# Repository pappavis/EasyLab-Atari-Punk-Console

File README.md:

Een poging om retro 'n 6581-SID chip na te bou met 555-timers ICs.<br/>
== Atari Punk Console
Ontwerp: Michiel Erasmus

<br/>
<br/>

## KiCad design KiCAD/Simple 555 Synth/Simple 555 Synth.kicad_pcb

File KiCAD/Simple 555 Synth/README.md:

-- Simple 555 Synth / Atari Punk Console --<br/>
8bit synth werk-in-uitvoering.<br/>
Ontwikkelaar: Michiel Erasmus<br/>
Een APC is, simpel geseg, 'n noise generator. Deur slimme en snelle manipulasie van weerstande is dit moontlik om Commodore6 64-achtige geluide te maak, of selfs drumbeats.<br/>
<br/>
Oorpsonklike APC ontwikkeld deur Forrest Mims in 1984<br/>
<br/>
<br/>
<br/>
<br/>
#easylab4kids #e4kdh<br/>

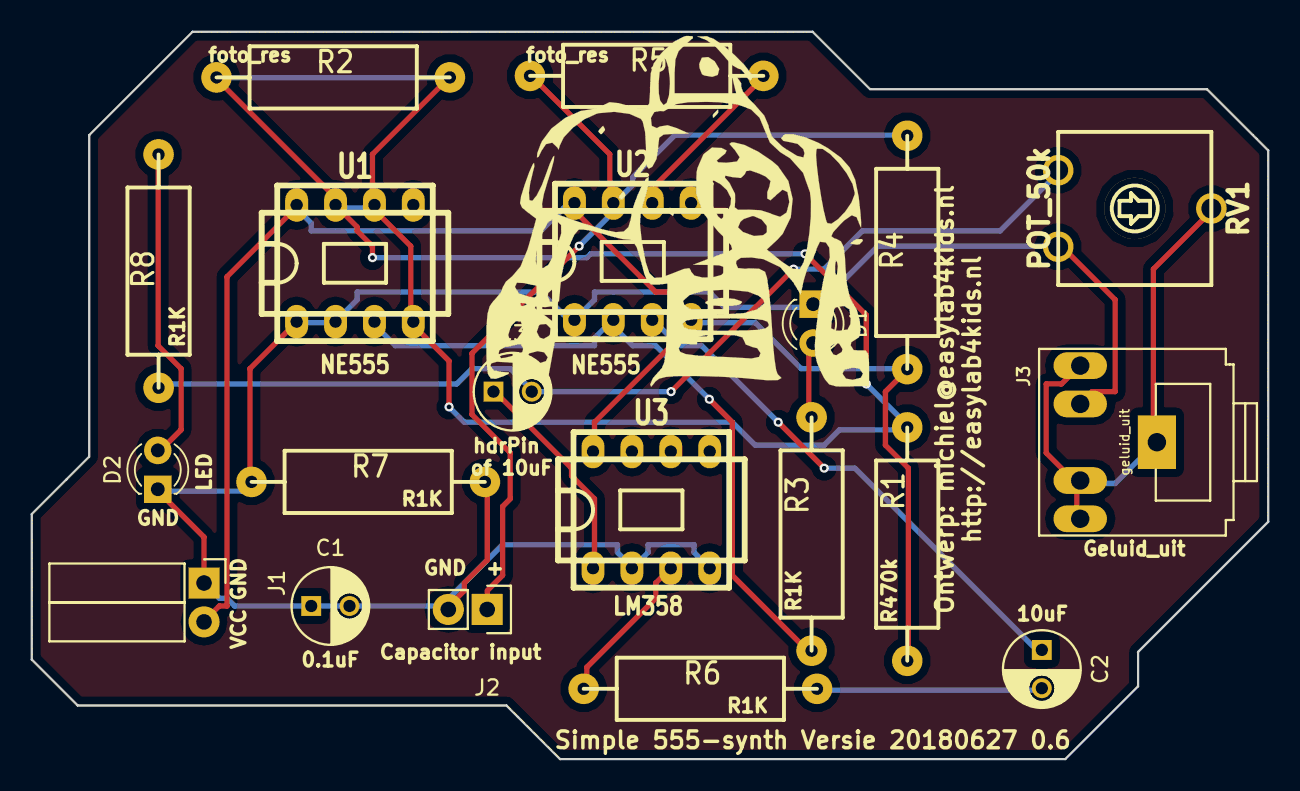
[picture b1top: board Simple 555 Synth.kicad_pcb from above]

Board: 2 copper layers, 80.8 x 47.5 mm, 21 parts (0 on the bottom side), 15 nets.

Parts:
C1: 0.1uF; C_Radial_D5_L11_P2.5
C2, C3: 10uF; C_Radial_D5_L11_P2.5
D1: LED1; LED_D3.0mm
D2: LED2; LED_D3.0mm
J1: Stroom; Socket_Strip_Angled_1x02
J2: CapacitorInput; Socket_Strip_Straight_1x02
J3: geluid_uit; Tayda_3.5mm_stereo_TRS_jack_A-853
P4: EasyLAB_LOGO; LOGO-sovjetSimpits
R1, R4: R470K; RC07
R2: R_PHOTO1; RC07
R3, R6, R7: R1K; RC07
R5: R_PHOTO2; RC07
R8: R1k; RC07
RV1: POT_50k; trimmer_ecp_ca9-v10
U1, U2: NE555; dil_8-300_socket
U3: LM358; dil_8-300_socket

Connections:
/VCC: J1.2, R1.1, R4.1, U1.8, U2.4, U2.8, U3.8
/cap1: J2.1, R4.2, R5.1, U2.7
/geluid1: R3.1, U1.3, U2.2
GND: C1.1, C1.2, D1.1, D2.1, J1.1, J2.2, J3.5, R7.1, R7.2, RV1.3, U1.1, U1.2, U2.1, U3.2, U3.4
unnamed: C2.1, U2.3
unnamed: C2.2, R6.2
unnamed: C3.1, U3.1
unnamed: C3.2, R8.1, RV1.1
unnamed: D1.2, R3.2
unnamed: D2.2, R8.2
unnamed: J3.1, J3.2, J3.3, J3.4, RV1.2
unnamed: R1.2, R2.1, U1.7
unnamed: R2.2, U1.4, U1.6
unnamed: R5.2, U2.6
unnamed: R6.1, U3.3

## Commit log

2018-04-05 :space_invader: Added .gitattributes & .gitignore files
2018-04-05 eerste commit
2018-06-18 Schema Versie 20180618 0.4
    LM358 OpAmp toegevoegd
2018-06-25 schema en printplaat Versie 20180625 0.6
2018-06-28 Printplaat Versie 20180627 0.6
    silkscreen teksten toegevoegd
